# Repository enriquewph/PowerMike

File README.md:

# PowerMike
Equipo para medir el consumo eléctrico de una vivienda.

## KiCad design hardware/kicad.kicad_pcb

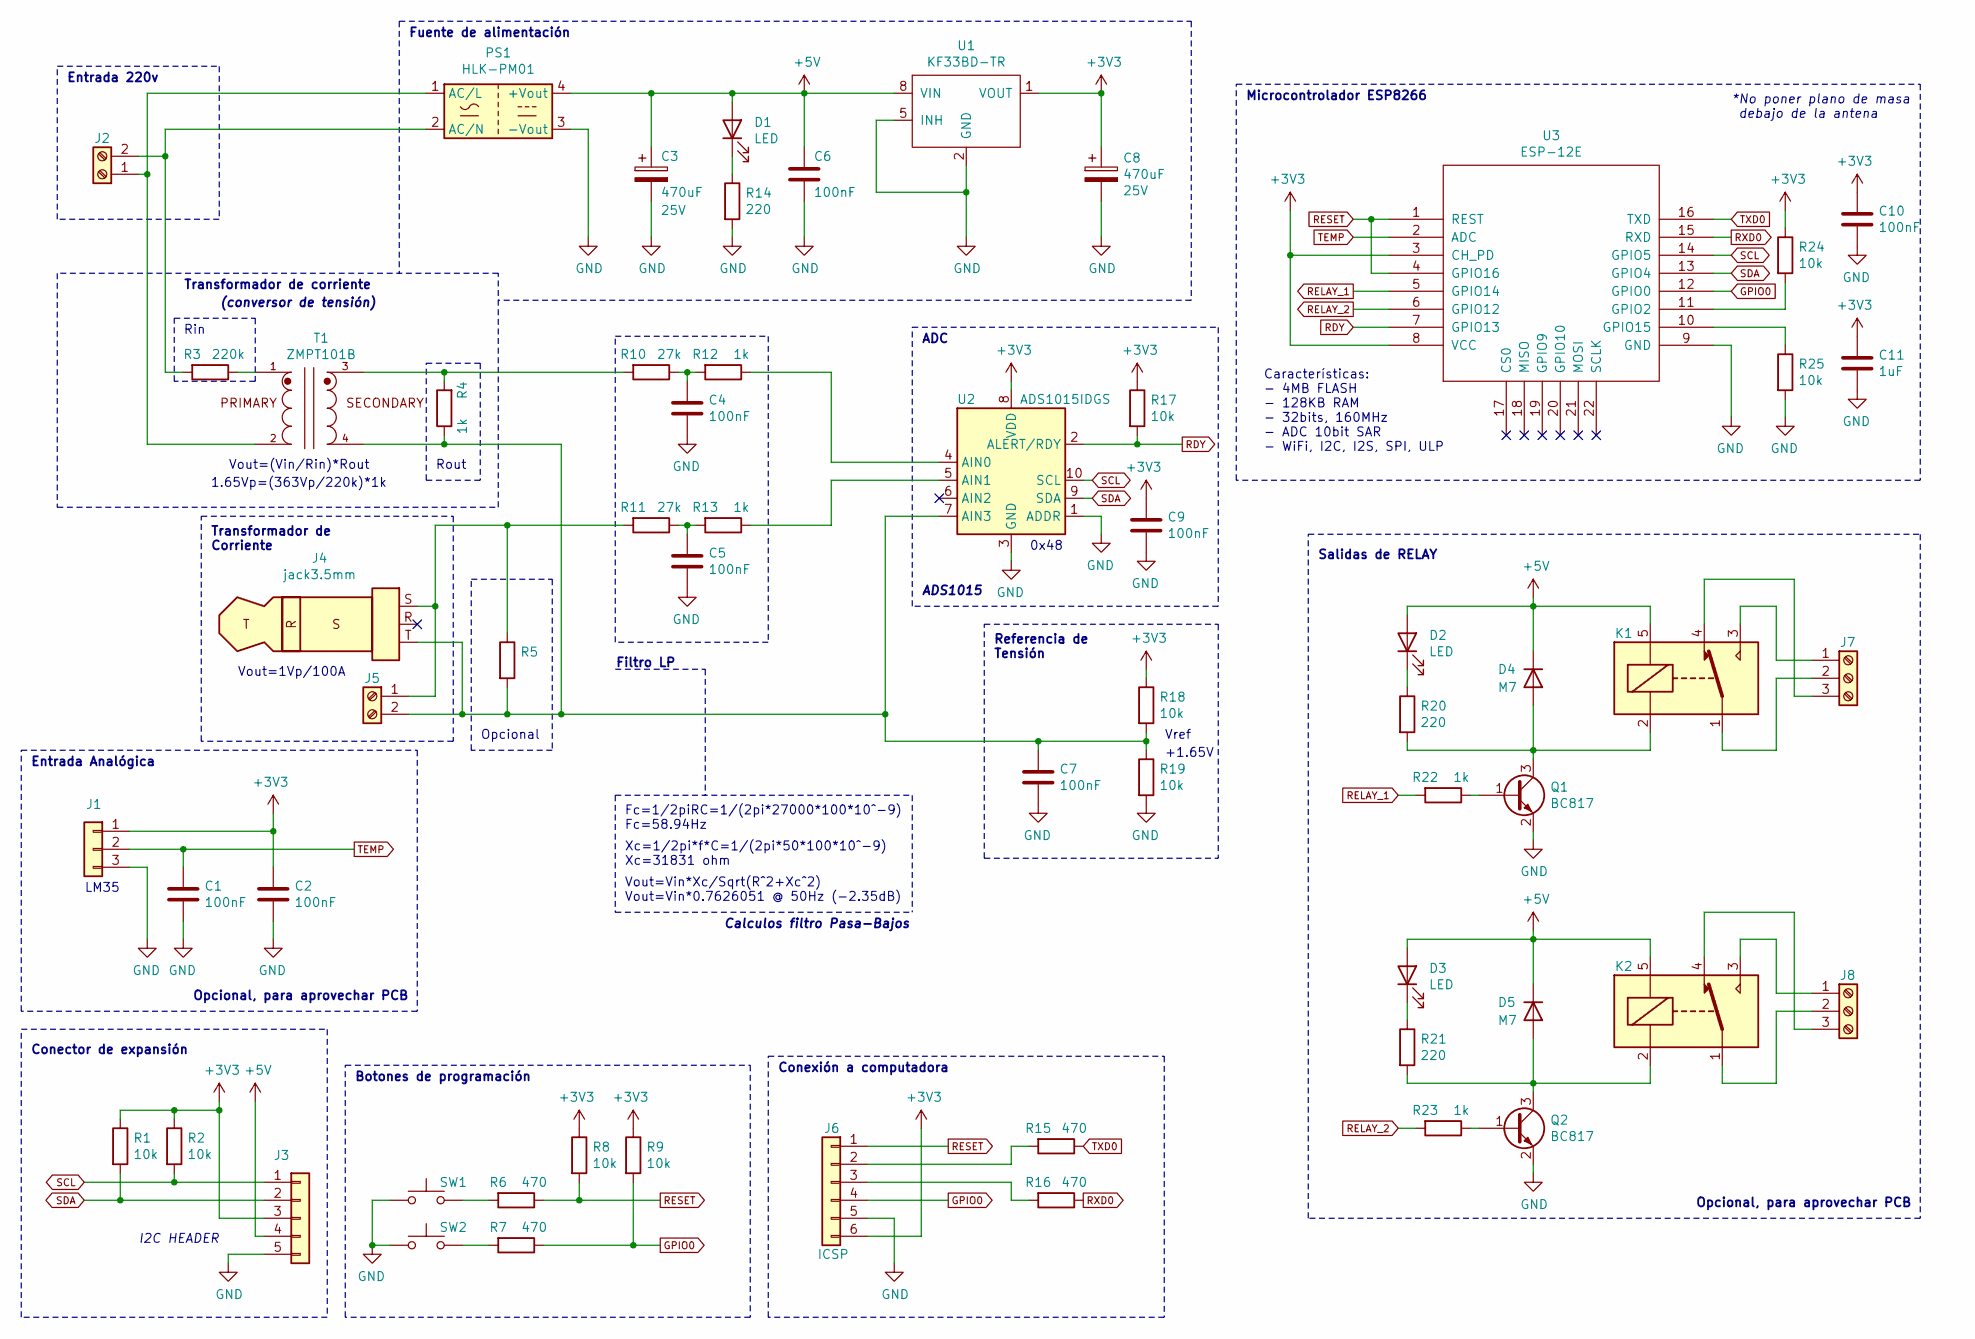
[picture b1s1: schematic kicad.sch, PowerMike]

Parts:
C1, C2, C4, C5, C6, C7, C9, C10: 100nF; C_1206_3216Metric_Pad1.33x1.80mm_HandSolder; Voltage 50V
C3, C8: 470uF; CAP_10x10_SMD_THT; Voltage 25V
C11: 1uF; C_1206_3216Metric_Pad1.33x1.80mm_HandSolder; Voltage 50V
D1, D2, D3: LED; LED_1206_3216Metric
D4, D5: M7; D_SMA_Handsoldering
J1: Conn_01x03; Molex_KK-254_AE-6410-03A_1x03_P2.54mm_Vertical
J2, J5: Screw_Terminal_01x02; TerminalBlock_bornier-2_P5.08mm
J3: Conn_01x05; Molex_KK-254_AE-6410-05A_1x05_P2.54mm_Vertical
J4: jack3.5mm; Jack_3.5mm_Ledino_KB3SPRS_Horizontal
J6: ICSP; PinSocket_1x06_P2.54mm_Vertical
J7, J8: Screw_Terminal_01x03; TerminalBlock_bornier-3_P5.08mm
K1, K2: RELAY 0510; Relay_SPDT_SANYOU_SRD_Series_Form_C
PS1: HLK-PM01; Converter_ACDC_HiLink_HLK-PMxx
Q1, Q2: BC817; SOT-23
R1, R2, R8, R9, R17, R18, R19, R24, R25: 10k; R_1206_3216Metric
R3: 220k; R_1206_3216Metric
R4, R12, R13, R22, R23: 1k; R_1206_3216Metric
R5: ?; R_1206_3216Metric
R6, R7, R15, R16: 470; R_1206_3216Metric
R10, R11: 27k; R_1206_3216Metric
R14, R20, R21: 220; R_1206_3216Metric
SW1, SW2: SW_Push; SW_PUSH_6mm
T1: ZMPT101B
U1: KF33BD-TR; SO-8_3.9x4.9mm_P1.27mm
U2: ADS1015IDGS; TSSOP-10_3x3mm_P0.5mm
U3: ESP-12E; ESP-12E_SMD

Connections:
+3V3: C2.1, C8.1, C9.1, C10.1, C11.1, J1.1, J3.3, J6.6, R1.1, R2.1, R8.1, R9.1, R17.1, R18.1, R24.1, U1.1 (VOUT), U2.8 (VDD), U3.3 (CH_PD), U3.8 (VCC)
+5V: C3.1, C6.1, D1.2 (A), D2.2 (A), D3.2 (A), D4.1 (K), D5.1 (K), J3.4, K1.5, K2.5, PS1.4 (+Vout), U1.8 (VIN)
GND: C1.2, C2.2, C3.2, C4.2, C5.2, C6.2, C7.2, C8.2, C9.2, C10.2, C11.2, J1.3, J3.5, J6.5, PS1.3 (-Vout), Q1.2 (E), Q2.2 (E), R14.2, R19.2, R25.2, SW1.1, SW2.1, U1.2 (GND), U1.3 (GND), U1.5 (INH), U1.6 (GND), U1.7 (GND), U2.1 (ADDR), U2.3 (GND), U3.9 (GND)
GPIO0: J6.4, R7.1, R9.2, U3.12 (GPIO0)
unnamed: C4.1, R10.1, R12.2
unnamed: C5.1, R11.1, R13.2
unnamed: C7.1, J4.T, J5.2, R4.1, R5.2, R18.2, R19.1, T1.4, U2.7 (AIN3)
unnamed: D1.1 (K), R14.1
unnamed: D2.1 (K), R20.1
unnamed: D3.1 (K), R21.1
unnamed: D4.2 (A), K1.2, Q1.3 (C), R20.2
unnamed: D5.2 (A), K2.2, Q2.3 (C), R21.2
unnamed: J2.1, PS1.1 (AC/L), T1.2
unnamed: J2.2, PS1.2 (AC/N), R3.2
unnamed: J4.S, J5.1, R5.1, R11.2
unnamed: J6.2, R15.2
unnamed: J6.3, R16.2
unnamed: J7.1, K1.3
unnamed: J7.2, K1.1
unnamed: J7.3, K1.4
unnamed: J8.1, K2.3
unnamed: J8.2, K2.1
unnamed: J8.3, K2.4
unnamed: Q1.1 (B), R22.1
unnamed: Q2.1 (B), R23.1
unnamed: R3.1, T1.1
unnamed: R6.2, SW1.2
unnamed: R7.2, SW2.2
unnamed: R4.2, R10.2, T1.3
unnamed: R12.1, U2.4 (AIN0)
unnamed: R13.1, U2.5 (AIN1)
unnamed: R24.2, U3.11 (GPIO2)
unnamed: R25.1, U3.10 (GPIO15)
RDY: R17.2, U2.2 (ALERT/RDY), U3.7 (GPIO13)
RELAY_1: R22.2, U3.5 (GPIO14)
RELAY_2: R23.2, U3.6 (GPIO12)
RESET: J6.1, R6.1, R8.2, U3.1 (REST), U3.4 (GPIO16)
RXD0: R16.1, U3.15 (RXD)
SCL: J3.1, R2.2, U2.10 (SCL), U3.14 (GPIO5)
SDA: J3.2, R1.2, U2.9 (SDA), U3.13 (GPIO4)
TEMP: C1.1, J1.2, U3.2 (ADC)
TXD0: R15.1, U3.16 (TXD)

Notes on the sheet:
LM35
I2C HEADER
0x48
Opcional
Vout=(Vin/Rin)*Rout
Rin
Rout
1.65Vp=(363Vp/220k)*1k
Vref
+1.65V
Opcional, para aprovechar PCB
Conexión a computadora
Botones de programación
Conector de expansión
Vout=1Vp/100A
Filtro LP
Fc=1/2piRC=1/(2pi*27000*100*10^-9) Fc=58.94Hz
Xc=1/2pi*f*C=1/(2pi*50*100*10^-9) Xc=31831 ohm
Vout=Vin*Xc/Sqrt(R^2+Xc^2) Vout=Vin*0.7626051 @ 50Hz (-2.35dB)
Calculos filtro Pasa-Bajos
Microcontrolador ESP8266
Características: - 4MB FLASH - 128KB RAM - 32bits, 160MHz - ADC 10bit SAR - WiFi, I2C, I2S, SPI, ULP
Entrada 220v
Fuente de alimentación
ADC
Referencia de Tensión
Transformador de Corriente
Transformador de corriente
(conversor de tensión)
ADS1015
*No poner plano de masa debajo de la antena
Salidas de RELAY
Entrada Analógica

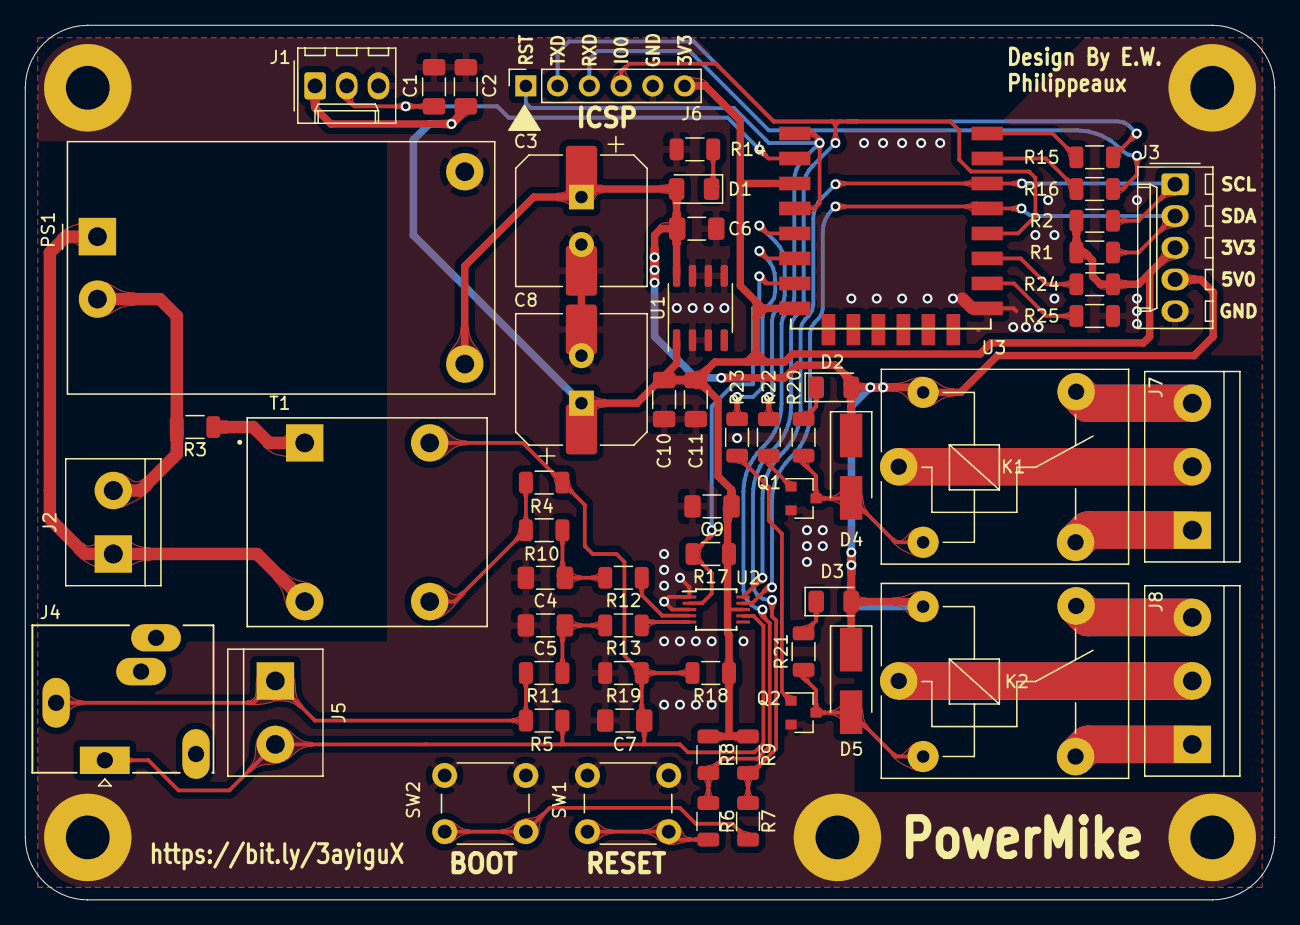
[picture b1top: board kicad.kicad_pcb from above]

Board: 2 copper layers, 100.0 x 70.0 mm, 60 parts (0 on the bottom side), 42 nets.

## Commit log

2021-09-26 Basado en proyecto antiguo
2021-09-26 Agregar libreria ESP8266
2021-09-26 cambios varios, agregado esp-12e
2021-09-26 esquema anotado
2021-09-26 demasiados cambios mi loco
2021-09-27 quiero dormir culiaaaa
2021-10-13 Esquematico final del proyecto.
2021-10-13 Diseño de pcb arrancado
2021-10-13 algo ruteado
2021-10-13 mas ruteado
2021-10-14 terminado ruteado principal
2021-10-14 Gerber exportado a .ZIP para JLCPCB
2021-10-14 Exportar step, pick&place, sch, bom
2021-10-14 Exportar step, pick&place, sch, bom (de nuevo)
2021-10-14 Exportar step, pick&place, sch, bom (de nuevo x2)
2022-03-10 Reorganizacion del repo
2022-03-10 'mean' may be used uninitialized in this function [-Wmaybe-uninitialized]
2022-03-10 ota funcionando
2022-03-10 Usar smartconfig para setup wifi
2022-03-11 grandes avances en la conectividad
